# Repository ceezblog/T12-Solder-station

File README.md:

# T12-Solder-station

Just another Solder station using ATMega328 (or variant)

## 1. Main board
- Support only T12 tip that has ~4ohm~ 8ohm heater
- Only work with ATMega168, ATMega328 or newer ATMega328PB
- Use IRF4905 (P-channel) to turn on/off heat element
- Use LMV321 for amplifying thermocouple voltage, not the best but cheap and reliable
- Use buck converter mini360 and linear regulator AMS1117 for high efficiency
- Encoder to control the temperature
- Use homemade opto switch, just a pair of IR LED and IR Reciever Diode (or phototransistor)
- Only need 2 wires to the tip's heat element

Pdf version here <a href='PCB/SolderStation_r0.5.pdf'>SolderStation_r0.5.pdf</a>

## 2. Switching PSU
- The 3D printed enclosure only supports this power supply model WX-DC2412, search aliexpress for "WX-DC2412 24V 4A"
- There are a few variants of this power supply have the same mounting holes which work just fine
- Always pick PSU 30% more power capable when your system full-load, ie: full-load 3A -> choose 4A PSU
- Laptop adaptor usually is 19V, using 8ohm tip -> 45w, while 24V PSU will delivery 72w at the tip
- It's better if you have earth prong from main AC 240V connect to the tip, but not neccessary
- Just a warm note: Do not attemp to modify or fix switching PSU, don't try messing with AC 240V

## 4. Display
- Only support LCD0802 - 8 char 2 line Character LCD, the main board was designed to piggyback on the LCD
- It is possible to use SSD1306 display via I2C or bitbang SPI for ILI9341 display controller but I haven't written code for this. 
- The 0802 is way nicer in my opinion
- PCB was designed for direct PCB to PCB plug-in (dupon header male and female) to the 14pin version of LCD0802

- There is 16pin version of LCD0802, which offset the pins. This won't be direct plug-in. It can be done but a bit of hack-ish solution:
  - Solder a tall header (2x7) and bend all 14 metal pins in an awkward way so that 4 screws in the corner would be in the right spot.
  - 2 extra pins (pin 15-16) are for the backlight and are not connected to controller blob. So the code won't be able to turn on/off backlight at will. There are 2 jumpers near the backlight LED (that connects to the LED and to the controller blob), just short those 2 jumpers and don't touch other jumpers. In my case, it is J3 and J4. Different vendors have different markings.
  - While you are there, replace 0R with 330R to lower down backlight current draw as well. It probably is 100R and 0R which I find a bit high (about 25mA @ 5V for white LED). Comfortable range for a small LED like that is around 5-20mA which your eyes won't be able to tell the difference in brightness, but your phone's camera will say otherwise.

## 5. Enclosure
- All 3D printed, except for the rubber feet to stop this box from sliding when pressing power button
- Housing a nice Switching PSU, no need for discrete power brick which you can't turn off from this box
- Include stand for the handle with docking mechanism using homemade opto switch
- Include opto switch housing, just need a pair of IR LED and IR receiver diode.

## 6. Firmware and calibration
- Using Arduino IDE and MiniCore for ATMEGA328PB (new variant that you can buy readily these day - 2023) while classic Arduino is ATMEGA328
- There are main firmware and calibration firmware for you to play with your own calibration
- Only ATMega328 and variant is supported because of low level code to config timer, pwm, interrupts...
- Only three libraries are used: **avr/interrupt.h, EEPROM.h and LiquidCrystal.h**
- Thermocouple in T12 tip is unknown, not K-type nor C-type, so you can't really use off-the-shelf themocouple amplifier
- I calibrate it by tabulating ADC readings against multiple temperatures, then plotting the chart in excel to find the trend equation: T = ADC*0.403 + 49.6
- This formular only applies to the amplifier that has gain of 471V/V and 8ohm T12 tip, if you have 4ohm tip, use with caution
- The downside of 10bit ADC is we cannot measure anything below 48mV which is around 50°C
- This guy has some nice work on debunk the myth T12 tip is K-type https://hackaday.io/project/94905-hakko-revenge/log/144548-hakko-t12-thermocouple-is-not-type-k
- ~Mine is a bit glitchy with EEPROM, sometime it doesn't remember docking function is ON after power off~ I just had a bad M328PB chip
- Doesn't implement any thermal runaway protection, but code such feature is not that hard:
  + At every tick, check if temp increase while powering - Heater dead or wrong pin connected if temperature stays the same
  + Check temperature difference if too great after 3-5s heat up - Probably different thermocouple in the tip
 
## 7. T12 Handle
- It would work with pretty much any T12 handle you can buy, but the stand probably won't accept many of them
- I have 2 stand designs for handles I have, check the cross section diameter of the handle before print
- If you want the original aviation GX plug come with the handle, then just short J5 by a jumper and by-pass check for handle
- A standalone iron handle stand <a href="https://ceezblog.com/revisit-my-homemade-t12-soldering-station">blog post at ceezblog.com</a>
 
 ## 8. Put everything together

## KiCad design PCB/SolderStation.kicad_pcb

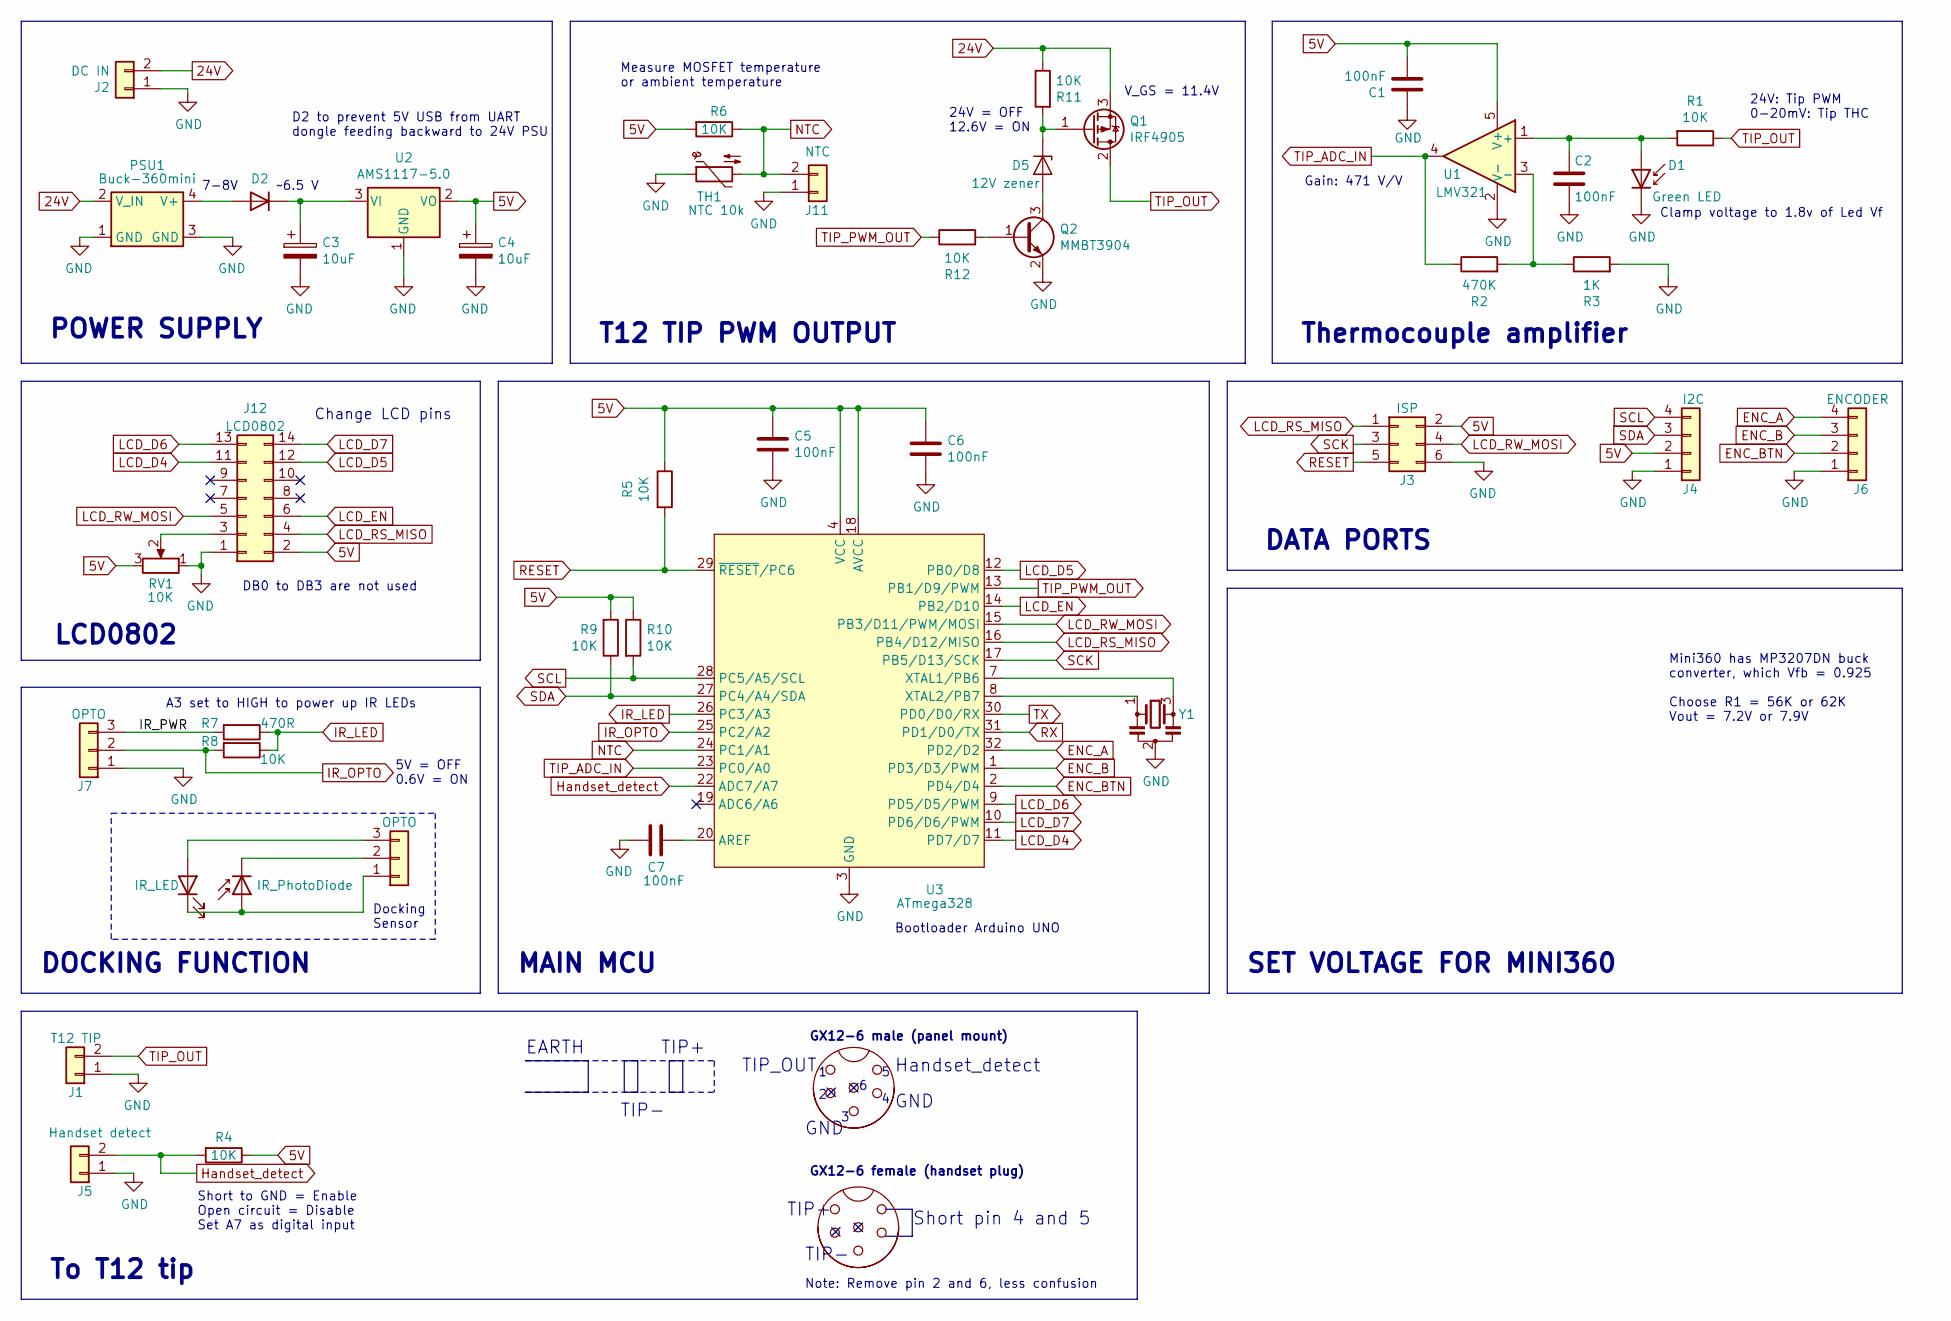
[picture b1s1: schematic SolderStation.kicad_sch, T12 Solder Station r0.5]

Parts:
C1, C2, C5, C6, C7: 100nF; C_0805_2012Metric
C3, C4: 10uF; CP_EIA-3528-12_Kemet-T
D1: Green LED; LED_0805_2012Metric
D2: Schottky; D_SMB
D3: IR_LED
D4: IR_PhotoDiode
D5: 12V zener; D_SOD-323
J1: T12 TIP; PinSocket_1x02_P2.54mm_Vertical
J2: DC IN; PinSocket_1x02_P2.54mm_Vertical
J3: ISP; PinHeader_2x03_P2.54mm_Vertical
J4: I2C; JST_XH_B4B-XH-A_1x04_P2.50mm_Vertical
J5: Handset detect; JST_XH_B2B-XH-A_1x02_P2.50mm_Vertical
J6: ENCODER; JST_XH_B4B-XH-A_1x04_P2.50mm_Vertical
J7, J8: OPTO; JST_XH_B3B-XH-A_1x03_P2.50mm_Vertical
J9: Aviation-GX12-6; ESD-Logo_6.6x6mm_SilkScreen
J10: Aviation-GX12-6; WEEE-Logo_4.2x6mm_SilkScreen
J11: NTC; JST_XH_B2B-XH-A_1x02_P2.50mm_Vertical
J12: LCD0802
PSU1: Buck-360mini; Mini360_DC-DC
Q1: IRF4905; TO-220-3_Minimal
Q2: MMBT3904; SOT-23
R1, R4, R5, R6, R8, R9, R10, R11, R12: 10K; R_0805_2012Metric
R2: 470K; R_0805_2012Metric
R3: 1K; R_0805_2012Metric
R7: 470R; R_0805_2012Metric
RV1: 10K; Potentiometer_Bourns_3266P_Horizontal
TH1: NTC 10k; R_0805_2012Metric
U1: LMV321; SOT-23-5
U2: AMS1117-5.0; SOT-223-3_TabPin2
U3: ATmega328; TQFP-32_7x7mm_P0.8mm
Y1: Resonator_Small; Resonator_SMD_muRata_CSTxExxV-3Pin_3.0x1.1mm

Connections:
5V: C1.2, C4.1, C5.1, C6.1, J3.2, J4.2, J12.2, R4.1, R5.1, R6.2, R9.2, R10.1, RV1.3, U1.5 (V+), U2.2 (VO), U3.4 (VCC), U3.6 (VCC), U3.18 (AVCC)
24V: J2.2, PSU1.2 (V_IN), Q1.3 (S), R11.1
/IR_PWR: J7.3, R7.2
ENC_A: J6.4, U3.32 (PD2/D2)
ENC_B: J6.3, U3.1 (PD3/D3/PWM)
ENC_BTN: J6.2, U3.2 (PD4/D4)
GND: C1.1, C2.2, C3.2, C4.2, C5.2, C6.2, C7.2, D1.1 (K), J1.1, J2.1, J3.6, J4.1, J5.1, J6.1, J7.1, J11.1, J12.1, PSU1.1 (GND), PSU1.3 (GND), Q2.2 (E), R3.2, RV1.1, TH1.1, U1.2 (V-), U2.1 (GND), U3.3 (GND), U3.5 (GND), U3.21 (GND), Y1.2
Handset_detect: J5.2, R4.2, U3.22 (ADC7/A7)
IR_LED: R7.1, R8.1, U3.26 (PC3/A3)
IR_OPTO: J7.2, R8.2, U3.25 (PC2/A2)
LCD_D4: J12.11, U3.11 (PD7/D7)
LCD_D5: J12.12, U3.12 (PB0/D8)
LCD_D6: J12.13, U3.9 (PD5/D5/PWM)
LCD_D7: J12.14, U3.10 (PD6/D6/PWM)
LCD_EN: J12.6, U3.14 (PB2/D10)
LCD_RS_MISO: J3.1, J12.4, U3.16 (PB4/D12/MISO)
LCD_RW_MOSI: J3.4, J12.5, U3.15 (PB3/D11/PWM/MOSI)
NTC: J11.2, R6.1, TH1.2, U3.24 (PC1/A1)
unnamed: C2.1, D1.2 (A), R1.2, U1.1 (+)
unnamed: D2.2 (A), PSU1.4 (V+)
unnamed: C3.1, D2.1 (K), U2.3 (VI)
unnamed: D3.1 (K), D4.2 (A), J8.1
unnamed: D3.2 (A), J8.3
unnamed: D4.1 (K), J8.2
unnamed: D5.2 (A), Q2.3 (C)
unnamed: D5.1 (K), Q1.1 (G), R11.2
unnamed: J12.3, RV1.2
unnamed: Q2.1 (B), R12.2
unnamed: R2.2, R3.1, U1.3 (-)
unnamed: C7.1, U3.20 (AREF)
unnamed: U3.7 (XTAL1/PB6), Y1.3
unnamed: U3.8 (XTAL2/PB7), Y1.1
RESET: J3.5, R5.2, U3.29 (~RESET/PC6)
RX: U3.31 (PD1/D0/TX)
SCK: J3.3, U3.17 (PB5/D13/SCK)
SCL: J4.4, R10.2, U3.28 (PC5/A5/SCL)
SDA: J4.3, R9.1, U3.27 (PC4/A4/SDA)
TIP_ADC_IN: R2.1, U1.4, U3.23 (PC0/A0)
TIP_OUT: J1.2, Q1.2 (D), R1.1
TIP_PWM_OUT: R12.1, U3.13 (PB1/D9/PWM)
TX: U3.30 (PD0/D0/RX)

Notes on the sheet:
Mini360 has MP3207DN buck converter, which Vfb = 0.925 Choose R1 = 56K or 62K Vout = 7.2V or 7.9V
Note: Remove pin 2 and 6, less confusion
Thermocouple amplifier
POWER SUPPLY
Measure MOSFET temperature or ambient temperature
5V = OFF 0.6V = ON
GND
DB0 to DB3 are not used
~6.5 V
TIP_OUT
Docking Sensor
DOCKING FUNCTION
A3 set to HIGH to power up IR LEDs
MAIN MCU
TIP-
Gain: 471 V/V
Change LCD pins
EARTH
7-8V
24V: Tip PWM 0-20mV: Tip THC
24V = OFF 12.6V = ON
GX12-6 male (panel mount)
To T12 tip
Short to GND = Enable Open circuit = Disable Set A7 as digital input
D2 to prevent 5V USB from UART dongle feeding backward to 24V PSU
Handset_detect
T12 TIP PWM OUTPUT
LCD0802
V_GS = 11.4V
Clamp voltage to 1.8v of Led Vf
Bootloader Arduino UNO
TIP+
Short pin 4 and 5
GX12-6 female (handset plug)
SET VOLTAGE FOR MINI360
DATA PORTS

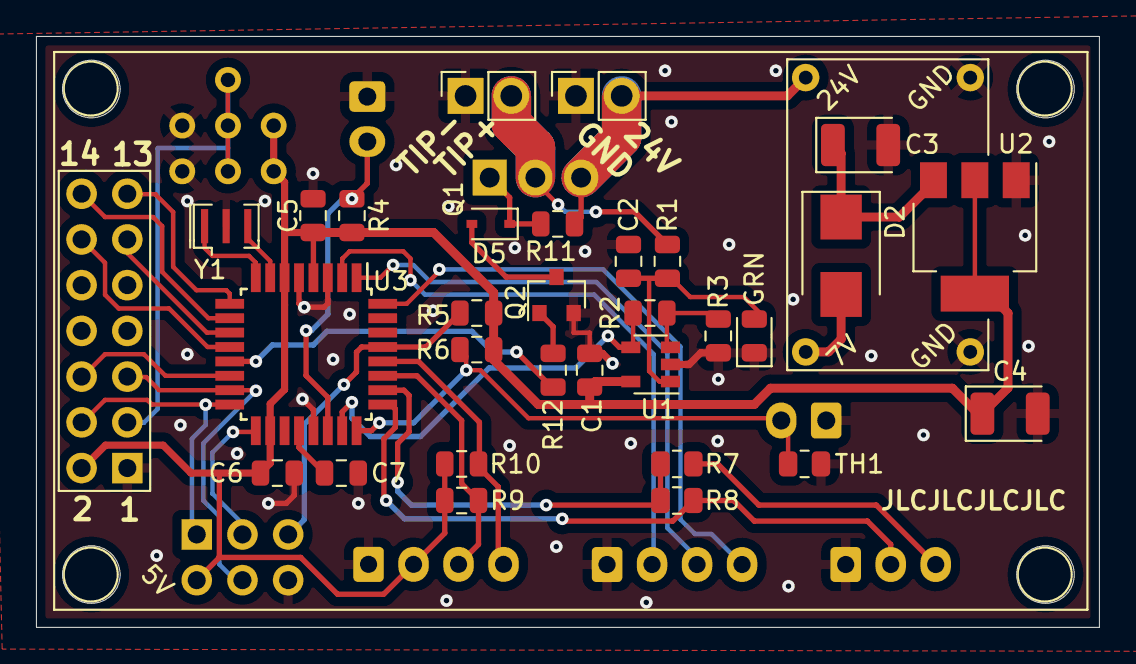
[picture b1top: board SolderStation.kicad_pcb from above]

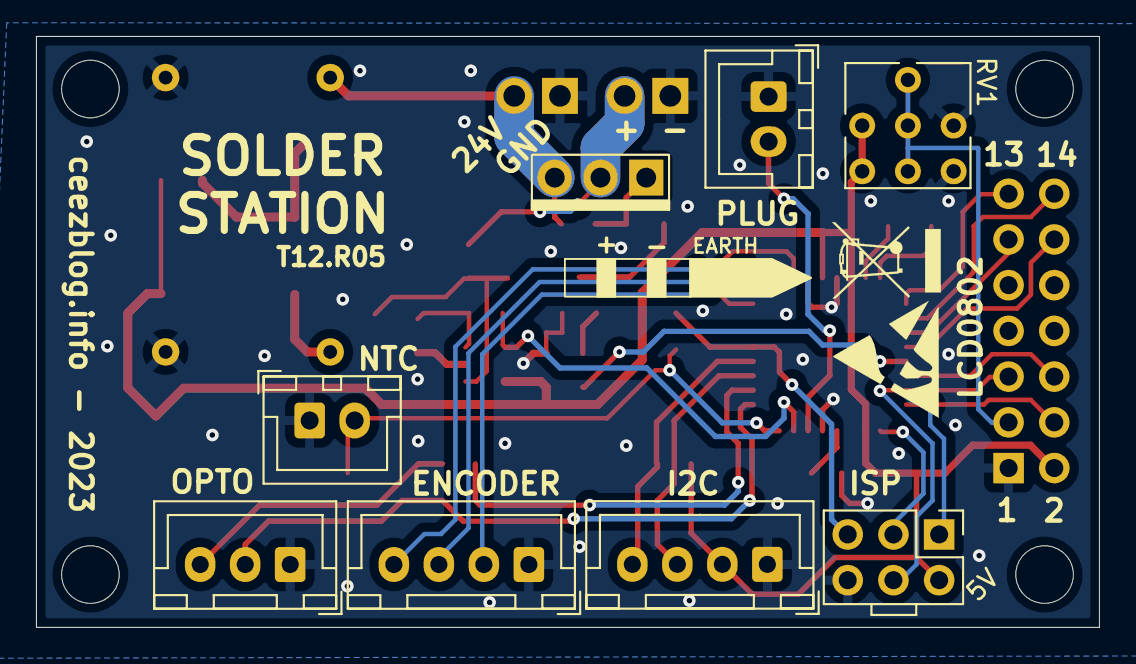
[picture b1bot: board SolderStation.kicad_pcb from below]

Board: 2 copper layers, 59.1 x 32.8 mm, 42 parts (10 on the bottom side), 36 nets.

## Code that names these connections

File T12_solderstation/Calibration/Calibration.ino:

///////////////////////////////////////////////////////////////////////////////
// T12 solder station - This is used for calibration
//	Cee'z 30 Mar 2023
//  
//	///////////////
//	// 23*C-1023 //    Mosfet temp - ADC value
//	// TD-24*C   //    Tip plugged - Docking - Tip temperature
//	///////////////
//
///////////////////////////////////////////////////////////////////////////////
// Target MCU: ATMega328 - bootloader Arduino UNO
// Clock: Ext 16MHz
//
// Character LCD 8x2
//		Fn:      5V+    GND   Enable  RS    R/W   Contrast  DB4 DB5 DB6 DB7	
//		Pin no:	 2      1     6       4     5     3         11  12  13  14
//		Arduino: 5v+    GND   D6      D5    D7    pot-10k   D10 D8  D12 D11
//
// The gain: (470K/1K)+1 = 471 v/v
// Take from the chart
// T = 0.47*ADC + 45.98
// T = 0.47*(ADC + 97.83)
// new data:
// T = 0.403*ADC + 49.60


//#define _DEBUG
#include <avr/interrupt.h>
#include <EEPROM.h>

// new configuration
#include <LiquidCrystal.h>
#define LCD_EN 6
#define LCD_RS 5
#define LCD_RW 7
#define LCD_D4 10
#define LCD_D5 8 
#define LCD_D6 12
#define LCD_D7 11

LiquidCrystal lcd(LCD_RS, LCD_RW, LCD_EN, LCD_D4, LCD_D5, LCD_D6, LCD_D7);

// custom chars
byte nextc[8] = {B00000,B01000,B01100,B01110,B01110,B01100,B01000,B00000};
byte stopc[8] = {B00000,B11011,B11011,B11011,B11011,B11011,B11011,B00000};
byte backc[8] = {B00000,B00010,B00110,B01110,B01110,B00110,B00010,B00000};

bool bSetUpdate;
int16_t tip_T;
int16_t tip_ADC;
int16_t air_T;

#define CHECK_TIP A7

void setup() {
  // put your setup code here, to run once:
  Serial.begin(9600);

  //add custom char;
  lcd.begin(8, 2);
  lcd.clear();
  lcd.createChar (0, nextc);
  lcd.createChar (1, stopc);
  lcd.createChar (2, backc);

  // Print a message to the LCD.
  lcd.setCursor(0, 0);
  lcd.print("T12 v0.1");
  lcd.setCursor(0, 1);
  lcd.print("Calibrate");  
  delay(2000);
  lcd.setCursor(0, 0);
  lcd.print("        ");
  lcd.setCursor(0, 1);
  lcd.print("        ");
    
  //EncoderSetup();
  
  //check if tip is 
  //pinMode(CHECK_TIP, INPUT_PULLUP);
  
  initTimer();
  // init variables

  //init PWM for controlling Heat element
  //initPWM_Tip();
  initOpto();

  //bAirUpdate = true;
  //bAir = true;
  
  //target_T = eepromRead_T();

}


// do not use any blocking function such as delay
void loop() 
{
  if (bSetUpdate)
  {
    read_T12();
    lcd_ADC_T();
    lcd_T();
    air_T = read_NTC();
    lcd_A();
    bSetUpdate = false; //updated
  }
  //isDocking();
  //isTipPlug();
}



////////////////////////////////
/// LCD write


void lcd_ADC_T()
{
  lcd.setCursor(3, 0);
  lcd.print(" ");
  lcd.print(tip_ADC);
  lcd.print("    ");
}
void lcd_T()
{
  lcd.setCursor(2, 1);
  lcd.print(" ");
  lcd.print(tip_T);
  //lcd.print((char)223);
  lcd.print("C  ");
}

void lcd_A()
{
  lcd.setCursor(0, 0);
  lcd.print((int)air_T);
  lcd.print("C");
}

////////////////////////////////
// T12 tip: read temp/ PWM out

// for docking check
#define OPTO A2
#define IR_LED A3
#define DOCK_TEMPERATURE 100


#define TIP_AN A0 // tip voltage
#define TIP_PWM 9 // D9
//#define NUM_OF_SAMPLE 4
#define SLEEP_T 100 // sleep temperature 60*C

//setup timer1 for PWM at D9
void initPWM_Tip()
{
  pinMode(TIP_PWM, OUTPUT);
  TCCR1A = _BV(COM1A1) | _BV(WGM10);
  TCCR1B = TCCR1B & B11111000 | B00000001;
  OCR1A = 0;
}

// T = 0.47*ADC + 45.98
// T = 0.403*ADC + 49.60

// Read T12 temp
void read_T12()
{
  int32_t T=0;
  for (int i=0;i<8; i++)
    T += analogRead(TIP_AN);
  //T = T>>3;
  tip_ADC = T>>3; //average by 8 reading
  T = 403*tip_ADC + 45980;
  tip_T = (int16_t)T/1000;
  //return (int16_t)T;
}

// increase target temp
void initOpto()
{
  digitalWrite(IR_LED, LOW); //turn off IR_LED
  pinMode(OPTO, INPUT);
  pinMode(IR_LED, OUTPUT);
}

bool isDocking()
{
  digitalWrite(IR_LED, HIGH); //turn on IR_LED
  bool ret = !digitalRead(OPTO); //if LOW == SLEEP
  digitalWrite(IR_LED, LOW); //turn off IR_LED
  return ret;
}


////////////////////////////////
/// READ THERMISTOR

#define SERIES_RESISTOR 10000
#define VCC 4950
#define NTC_NOMINAL 10000      
#define NTC_TEMP_NOMINAL 25   

#define B_COEFF 3950

#define NUMSAMPLES 8
#define NTC_AN A1


float read_NTC()
{
  float Vo=0;
  //read n times
  for (int i=0; i< NUMSAMPLES; i++) 
    Vo += analogRead(NTC_AN);
    
  Vo /= NUMSAMPLES; //averaging
  
  // convert to resistance R_NTC
  Vo = SERIES_RESISTOR /(1023/Vo  - 1);     // 10K * (ADC - 1) / 1023
    
  float NTC_temp;

  // T_NTC = 1/ [ ln(R_NTC/Ro) / B + 1/(To) ]  deg Kelvin
  // 1/T_NTC = ln(R_NTC /Ro) / B + 1/To, where T_NTC and To in Kelvin
 
  NTC_temp = Vo / NTC_NOMINAL;                    // (R/Ro)
  NTC_temp = log(NTC_temp);                       // ln(R/Ro)
  NTC_temp /= B_COEFF;                            // 1/B * ln(R/Ro)
  NTC_temp += 1.0 / (NTC_TEMP_NOMINAL + 273.15);  // + (1/To)
  NTC_temp = 1.0 / NTC_temp;                      // Invert
  NTC_temp -= 273.15;                             // convert to C

  return NTC_temp;
}

////////////////////////////////
/// TIMER STUFF

uint16_t HeaterTick;
uint16_t AirTick;
uint16_t OptoTick;

// UPDATE RATE
// Heater 
#define HEATER_RATE 20
#define AIR_RATE 1000
#define OPTO_CHECK_RATE 5

void resetAirTick()
{
  //AirTick =0;
  //bAirUpdate = false;
}

// Call every 50ms
ISR(TIMER2_OVF_vect)        
{
  TCNT2 = 1310;   // preload counter for 20Hz
  HeaterTick++;
  AirTick++;
  OptoTick++;
  
  if (HeaterTick > HEATER_RATE) //update every 10 ticks
  {
    HeaterTick =0;
    bSetUpdate = true;
  }
}

/// Setup timer for 20Hz (or 50ms each INT event)
void initTimer()
{
  //initialize timer1 
  noInterrupts();           // disable all interrupts
  TCCR2A = 0;
  TCCR2B = 0;
  
  TCNT2 = 1310;            // preload timer 65536-16MHz/256/20Hz
  TCCR2B = TCCR2B & B11111000 | B00000111;    // 30.6Hz
  TIMSK2 |= (1 << TOIE1);   // enable timer overflow interrupt
  interrupts();             // enable all interrupts
}

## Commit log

2023-04-20 Add files via upload
    Add firmware
2023-04-20 Add files via upload
    Add LCD0802 dimensions
2023-10-01 Add files via upload
    Update opto docking function:
    - Dock/undock 3 times would trigger docking function
    - Add 2 more sleep temperatures for better wake up response time:
    + Limit to 200degC after docking
    + Limit to 100degC after 120s docking
    + Turn off heater after 15 minutes
2023-10-01 Add files via upload
    Fix: only turn on Opto when doing check
2023-10-01 Add files via upload
    Update opto docking function:
    - Dock/undock 3 times would trigger docking function
    - Add 2 more sleep temperatures for better wake up response time:
    + Limit to 200degC after docking
    + Limit to 100degC after 120s docking
    + Turn off heater after 15 minutes
2023-10-07 Add files via upload
    - Improve using experience
    - Quicker heat up from sleep
2023-10-07 Add files via upload
    - Upgrade project to Kicad 7.0
    - Improve schematic details
2023-10-09 Add files via upload
    Problem:
    Flickering between sleep and working while not docking
    Possible cause:
    When power up sensor by GPIO, it takes some time to
    + ramp up voltage at IR-LED for it to fully blast IR beam
    + IR Diode to fully reverse conduct to get LOW level
2023-10-22 Add files via upload
    Update diagram picture
2025-08-24 Add files via upload
    Add standalone iron handle stand
2025-08-24 Add files via upload
    Add standalone iron handle stand pictures
2025-08-24 Rename standalone iron handle stand.jpg to with standalone iron handle stand.jpg
2026-06-01 Enhance README with LCD0802 16pin variant
    Updated the README to clarify the 16-pin version of LCD0802 installation and backlight modifications.
